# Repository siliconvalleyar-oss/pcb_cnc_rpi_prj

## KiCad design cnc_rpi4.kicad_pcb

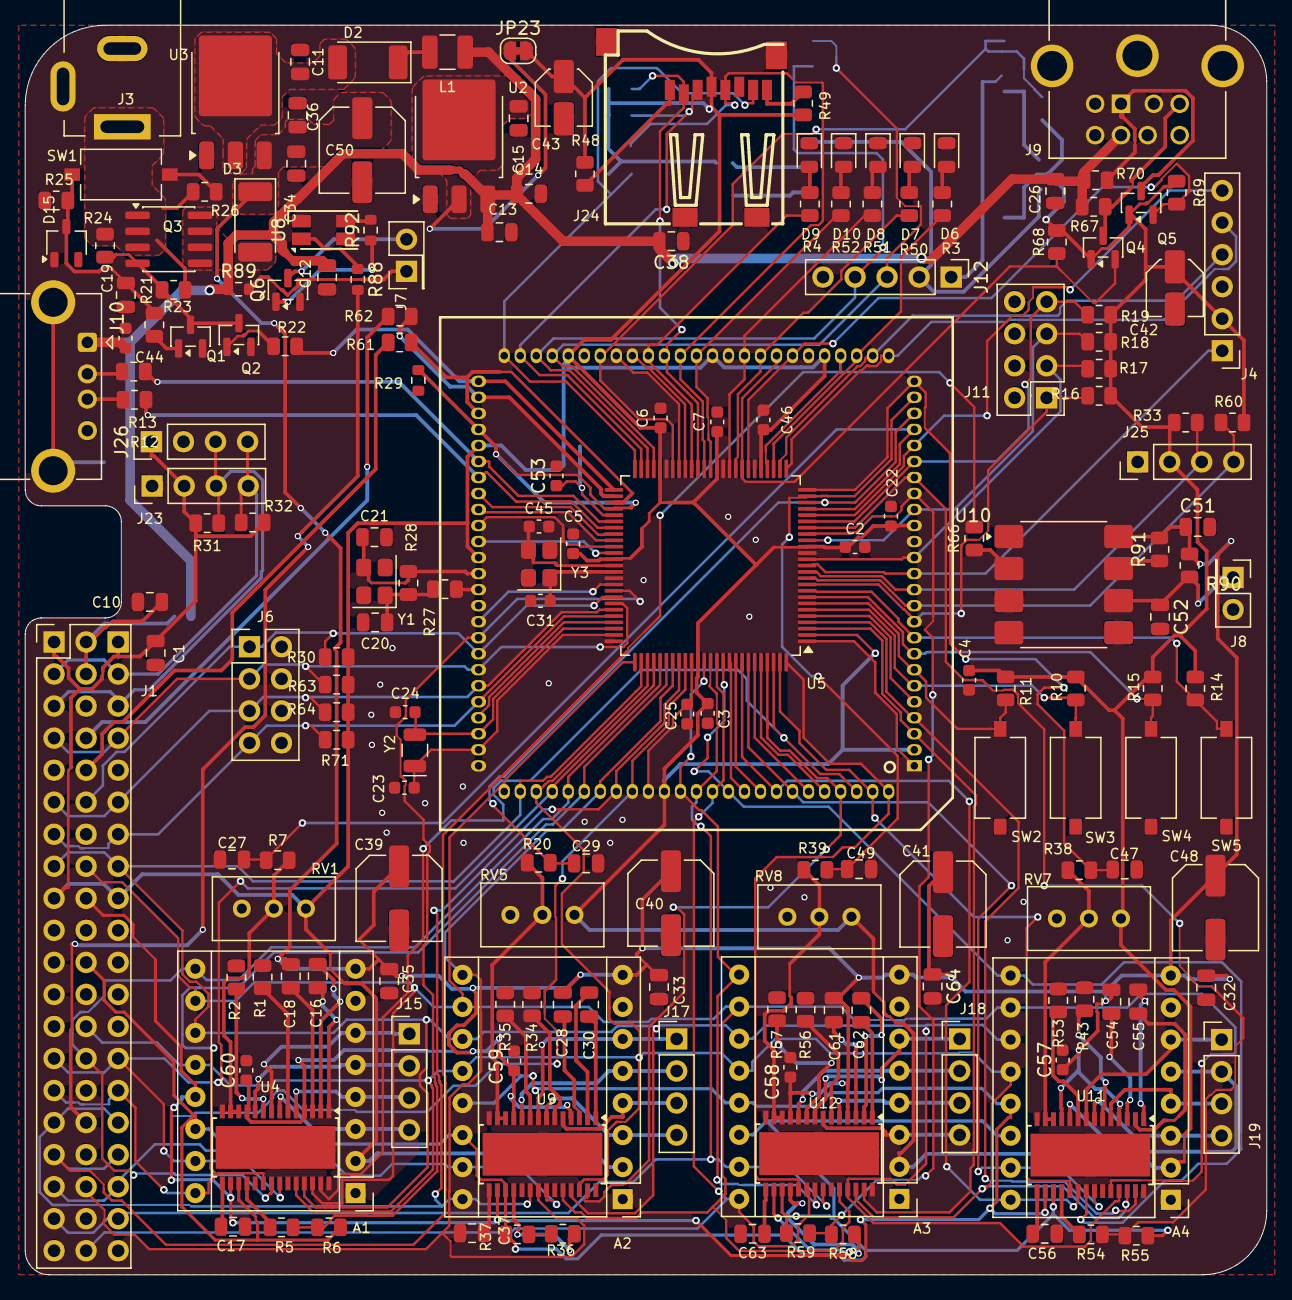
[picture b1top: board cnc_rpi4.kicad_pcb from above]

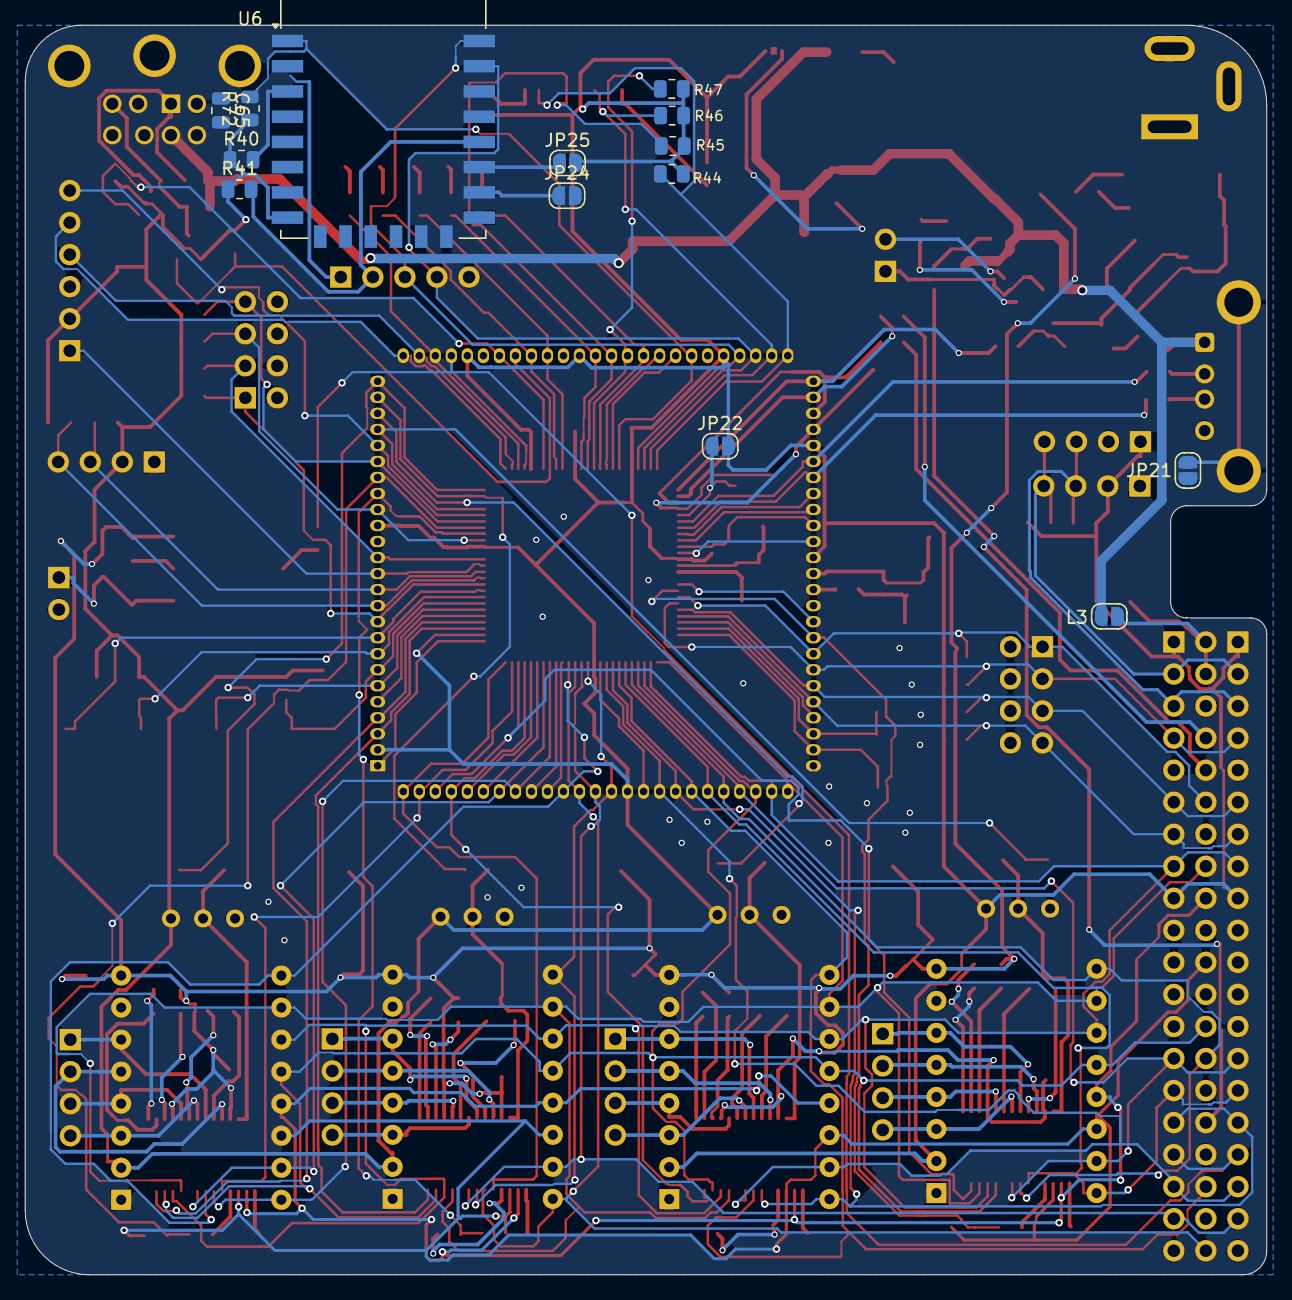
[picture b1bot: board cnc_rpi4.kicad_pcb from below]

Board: 2 copper layers, 98.4 x 99.1 mm, 202 parts (14 on the bottom side), 185 nets.

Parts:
A1, A2, A3, A4: Pololu_Breakout_A4988; Pololu_Breakout-16_15.2x20.3mm
C1, C10, C12, C13, C18, C19, C26, C27, C28, C29, C32, C33, C34, C35, C38, C47, C49, C51, C52, C54, C61, C64, C65: 100nf; C_0805_2012Metric
C2, C3, C4, C5, C6, C7, C22, C44, C57, C58, C59, C60: 100nf; C_0603_1608Metric
C11, C14, C15, C17, C36, C37, C56, C63: 4.7uf; C_0805_2012Metric
C16, C30, C55, C62: 10nf; C_0805_2012Metric
C20, C21: 15p; C_0805_2012Metric
C23, C24, C31, C45, C53: 15p; C_0603_1608Metric
C25, C46: 100; C_0603_1608Metric
C39, C40, C41, C48, C50: RVT100UF35V67RV0034; C_Elec_6.3x5.4
C42, C43: EFVH035ADA100M0454; C_Elec_4x5.4
D2, D3: 1N6858UR; D_MELF
D6, D7, D8, D9, D10: LED; D_0805_2012Metric
D15: D_Zener_Dual_CommonCathode_AAK_Split; TSOT-23
J1: Raspberry_Pi_4; Rpi_PinHeader_2x20_P2.54mm_Vertical
J3: PWR IN; BarrelJack_Kycon_KLDX-0202-xC_Horizontal
J4: icd; PinHeader_1x06_P2.54mm_Vertical
J6, J11: LIMITS; PinHeader_2x04_P2.54mm_Vertical
J7: Motor_1; PinHeader_2x01_P2.54mm_Vertical
J8: Motor_2; PinHeader_2x01_P2.54mm_Vertical
J9: Mini-DIN-6; MINIDIN6_TE_1658998-1
J10: USB_A; USB_A_Kycon_KUSBX-AS1N-B_Horizontal
J12: uart_programmer; PinHeader_1x05_P2.54mm_Vertical
J15, J17, J18, J19: pololu; PinHeader_1x04_P2.54mm_Vertical
J23, J25, J26: OLED SSD1306; PinHeader_1x04_P2.54mm_Vertical
J24: TF-001B
JP21, JP24, JP25: SolderJumper-2_P1.3mm_Open_RoundedPad1.0x1.5mm
JP22: usb_on; SolderJumper-2_P1.3mm_Open_RoundedPad1.0x1.5mm
JP23: 0; SolderJumper-2_P1.3mm_Bridged_RoundedPad1.0x1.5mm
L1: 100mh; L_1210_3225Metric
L3: 100mh; SolderJumper-2_P1.3mm_Open_RoundedPad1.0x1.5mm
Q1, Q2, Q6: BC847; SOT-23
Q3: IRF7404; SOIC-8_3.9x4.9mm_P1.27mm
Q4, Q5: 2N7002; SOT-23
R1, R2, R6, R34, R35, R37, R43, R53, R55, R56, R57, R59: 0.1r; R_0805_2012Metric
R3, R4, R31, R32, R50, R51, R52: 1k; R_0805_2012Metric
R5, R36, R54, R58: 1.5k; R_0805_2012Metric
R7, R20, R38, R39, R61, R62, R66, R67, R68, R69, R70, R90, R91: 100; R_0805_2012Metric
R10, R11, R14, R15, R33, R41, R44, R45, R46, R47, R48, R49, R60, R72: 2k2; R_0805_2012Metric
R12, R13, R40: 0; R_0805_2012Metric
R16, R17, R18, R19, R30, R63, R64, R71: 10k; R_0805_2012Metric
R21, R22: 10kr; R_0805_2012Metric
R23: 100K; R_0805_2012Metric
R24: 33K; R_0805_2012Metric
R25, R26: 100k; R_0805_2012Metric
R27: 1K; R_0805_2012Metric
R28: 1M; R_0805_2012Metric
R29: 0; R_0603_1608Metric
R88, R89, R92: 1k; R_0603_1608Metric
RV1, RV5, RV7, RV8: 10k Potentiometer_Trim_US; Potentiometer_Bourns_3296W_Vertical
SW1, SW2, SW3, SW4, SW5: K2-1107ST-A4SW-06; SW_Tactile_SPST_NO_Straight_CK_PTS636Sx25SMTRLFS
U1: PIC32MX795F512L-80x-PF; MA240011_Socket_TQFP100_100pin
U2: LM1117DT-3.3; TO-252-3_TabPin2
U3: LM1117DT-5.0; TO-252-3_TabPin2
U4, U9, U11, U12: DRV8825PWPR; HTSSOP-28-1EP_4.4x9.7mm_P0.65mm_EP3.4x9.5mm
U5: PIC32MX795F512L-80I_PF; TQFP-100_14x14mm_P0.5mm
U6: ESP-12E
U8: Optocoupler_DC_PhotoNPN_AKEC; Kingbright_KPS-3227
U10: 6N137S-TA1; SOP-8_6.605x9.655mm_P2.54mm
Y1, Y3: 8MHz SMD crystal oscillator ±10ppm ±30ppm SMD3225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; Crystal_SMD_3225-4Pin_3.2x2.5mm
Y2: Crystal_Small; Crystal_SMD_EuroQuartz_EQ161-2Pin_3.2x1.5mm

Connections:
+3V3: A1.2 (VDD), A2.2 (VDD), A3.2 (VDD), A4.2 (VDD), C1.1, C2.1, C3.1, C4.1, C5.1, C6.1, C7.1, C22.1, C42.1, C43.1, C46.1, J1.1 (3V3), J1.17 (3V3), J4.2, J23.2, J24.4 (VDD), J25.2, J26.1, JP22.2 (B), JP23.2 (B), JP25.2 (B), Q4.1 (G), Q5.1 (G), R10.1, R11.1, R14.1, R15.1, R16.1, R17.1, R18.1, R19.1, R30.1, R31.1, R32.1, R33.1, R40.1, R41.1, R44.2, R45.2, R46.2, R47.2, R48.2, R49.1, R60.1, R63.1, R64.1, R68.2, R69.2, R71.1, R72.1, RV1.1, RV5.1, RV7.1, RV8.1, U1.2 (VDD), U1.16 (VDD), U1.30 (AVDD), U1.37 (VDD), U1.46 (VDD), U1.55 (VUSB3V3), U1.62 (VDD), U1.86 (VDD), U5.2 (VDD), U5.16 (VDD), U5.30 (AVDD), U5.37 (VDD), U5.46 (VDD), U5.62 (VDD), U5.86 (VDD), U6.8 (VCC)
+5V: C12.1, C13.1, C14.2, C26.1, C38.2, C44.2, J9.4, J10.1 (VBUS), L1.2, L3.2, R67.2, R70.2, R89.1, U2.3 (VI)
/ANALOG_1: C27.1, R7.1, U1.22 (RB3), U5.22 (AN3/C2IN+/CN5/RB3)
/ANALOG_2: C29.1, R20.1, U1.23 (RB2), U5.23 (AN2/C2IN-/CN4/RB2)
/ANALOG_3: C49.1, R39.1, U1.24 (PGEC1/RB1), U5.24 (PGEC1/AN1/CN3/RB1)
/ANALOG_4: C47.1, R38.1, U1.25 (PGED1/RB0), U5.25 (PGED1/AN0/CN2/RB0)
/GPIO2_SDA: J1.3 (SDA_I2C1/GPIO02), J23.4, J26.4, R32.2
/GPIO3_SCL: J1.5 (SCL_I2C1/GPIO03), J23.3, J26.3, R31.2
/LED_a: R3.1, U1.28 (RA9), U5.28 (VREF-/CVREF-/AERXD2/PMA7/RA9)
/LED_b: R50.1, U1.34 (RB10), U5.34 (AN10/CVREFOUT/PMA13/RB10)
/LED_c: R51.1, U1.35 (RB11), U5.35 (AN11/ERXERR/AETXERR/PMA12/RB11)
/LED_d: R4.1, U1.41 (RB12), U5.41 (AN12/ERXD0/AECRS/PMA11/RB12)
/LED_e: R52.1, U1.38 (RA1/TCK), U5.38 (TCK/RA1)
/MCU/5VCC: C10.1, J1.2 (5V), J1.4 (5V), L3.1
/MS1: A1.10 (MS1), A2.10 (MS1), A3.10 (MS1), A4.10 (MS1), J1.16 (GPIO23/SDIO_CMD), U1.76 (RD1), U4.26 (MODE2), U5.76 (OC2/RD1), U9.24 (MODE0), U11.24 (MODE0), U12.24 (MODE0)
/MS2: A1.11 (MS2), A2.11 (MS2), A3.11 (MS2), A4.11 (MS2), J1.15 (GPIO22/SDIO_CLK), U1.77 (RD2), U4.25 (MODE1), U5.77 (OC3/RD2), U9.25 (MODE1), U11.25 (MODE1), U12.25 (MODE1)
/MS3: A1.12 (MS3), A2.12 (MS3), A3.12 (MS3), A4.12 (MS3), J1.26 (~CE1_SPI0/GPIO07), U1.78 (RD3), U4.24 (MODE0), U5.78 (OC4/RD3), U9.26 (MODE2), U11.26 (MODE2), U12.26 (MODE2)
/M_Rx: J1.10 (GPIO15/UART_RXD), R61.1
/M_Tx: J1.8 (GPIO14/UART_TXD), R62.1
/PIC32_SCL: J25.3, R33.2, U1.12 (RG8), U5.12 (ERXDV/AERXDV/ECRSDV/AECRSDV/SCL4/SDO2/U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)
/PIC32_SDA: J25.4, R60.2, U1.11 (RG7), U5.11 (ECRS/SDA4/SDI2/U3RX/PMA4/CN9/RG7)
/PS2_CLK: Q4.2 (S), R68.1, U1.33 (RB9), U5.33 (AN9/C2OUT/RB9)
/PS2_DATA: Q5.2 (S), R69.1, U1.32 (RB8), U5.32 (AN8/C1OUT/RB8)
/PWR_SIGNAL: R22.1, U1.51 (RF3), U5.51 (USBID/RF3)
/Pololu/IC4_dir: A4.16 (DIR), U1.93 (RE0), U5.93 (PMD0/RE0), U11.20 (DIR)
/Pololu/IC4_enable: A4.9 (~ENABLE), U1.90 (RG0), U5.90 (C2RX/PMD8/RG0), U11.21 (NENBL)
/Pololu/IC4_step: A4.15 (STEP), U1.94 (RE1), U5.94 (PMD1/RE1), U11.22 (STEP)
/RA6: U1.91 (RA6/TRCLK), U5.91 (TRCLK/RA6), U9.19 (DECAY)
/RA7: U1.92 (RA7/TRD3), U4.19 (DECAY), U5.92 (TRD3/RA7)
/RE2: U1.98 (RE2), U4.27 (nHOME), U5.98 (PMD2/RE2)
/RE3: U1.99 (RE3), U5.99 (PMD3/RE3), U11.19 (DECAY)
/RE4: U1.100 (RE4), U5.100 (PMD4/RE4), U12.19 (DECAY)
/RE5: U1.3 (RE5), U5.3 (PMD5/RE5), U12.27 (nHOME)
/RE6: U1.4 (RE6), U5.4 (PMD6/RE6), U11.27 (nHOME)
/RG13: U1.97 (RG13/TRD0), U5.97 (TRD0/RG13), U9.27 (nHOME)
/dir_1: A1.16 (DIR), J1.29 (GPCLK1/GPIO05), U1.81 (RD4), U4.20 (DIR), U5.81 (OC5/PMWR/CN13/RD4)
/dir_2: A2.16 (DIR), J1.31 (GPCLK2/GPIO06), U1.83 (RD6), U5.83 (ETXEN/PMD14/CN15/RD6), U9.20 (DIR)
/dir_3: A3.16 (DIR), J1.40 (GPIO21/SPI1_SCLK/PCM_DOUT), U1.89 (RG1), U5.89 (C2TX/ETXERR/PMD9/RG1), U12.20 (DIR)
/en_1: A1.9 (~ENABLE), J1.28 (ID_SC_I2C0/GPIO01), U1.80 (RD13), U4.21 (NENBL), U5.80 (ETXD3/PMD13/CN19/RD13)
/en_2: A2.9 (~ENABLE), J1.36 (GPIO16/SPI1_~CE2), U1.82 (RD5), U5.82 (PMRD/CN14/RD5), U9.21 (NENBL)
/en_3: A3.9 (~ENABLE), J1.38 (GPIO20/SPI1_MOSI/PCM_DIN/PWM1), U1.87 (RF0), U5.87 (C1RX/ETXD1/PMD11/RF0), U12.21 (NENBL)
/esp8266mod/FLASH_esp: J12.2, R41.2, U6.18 (GPIO0)
/esp8266mod/RST_esp: C65.1, R72.2, U1.44 (RB15), U5.44 (AN15/ERXD3/AETXD2/OCFB/PMALL/PMA0/CN12/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), U6.1 (~RST)
/esp8266mod/RXD_esp: J12.4, U1.48 (RD15), U5.48 (AETXD1/SCK3/U4TX/~U1RTS/CN21/RD15), U6.21 (GPIO3/RXD)
/esp8266mod/TDX_esp: J12.3, U1.47 (RD14), U5.47 (AETXD0/~SS3/U4RX/~U1CTS/CN20/RD14), U6.22 (GPIO1/TXD)
/flt_1: R5.2, R6.2, U1.67 (RA15), U5.67 (AETXEN/SDA1/INT4/RA15)
/flt_2: R36.2, R37.2, U1.66 (RA14), U5.66 (AETXCLK/SCL1/INT3/RA14)
/flt_3: R58.2, R59.2, U1.18 (RE8), U5.18 (AERXD0/INT1/RE8)
/flt_4: R54.2, R55.1, U1.19 (RE9), U5.19 (AERXD1/INT2/RE9)
/limit_1: J11.1, R16.2, U1.10 (RG6), U5.10 (ECOL/SCK2/U6TX/~U3RTS/PMA5/CN8/RG6)
/limit_2: J11.3, R17.2, U1.14 (RG9), U5.14 (ERXCLK/AERXCLK/EREFCLK/AEREFCLK/~SS2/U6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)
/limit_3: J11.5, R18.2, U1.17 (RA0/TMS), U5.17 (TMS/RA0)
/limit_4: J11.7, R19.2, U1.20 (RB5), U5.20 (AN5/C1IN+/VBUSON/CN7/RB5)
/limit_pi1: J1.12 (GPIO18/SPI1_~CE0/PCM_CLK/PWM0), J6.1, R30.2, U1.68 (RD8), U5.68 (RTCC/EMDIO/AEMDIO/IC1/RD8)
/limit_pi2: J1.7 (GPCLK0/GPIO04), J6.3, R63.2, U1.69 (RD9), U5.69 (~SS1/IC2/RD9)
/limit_pi3: J1.11 (GPIO17/SPI1_~CE1), J6.5, R64.2, U1.70 (RD10), U5.70 (SCK1/IC3/PMCS2/PMA15/RD10)
/limit_pi4: J1.13 (GPIO27/SDIO_DAT3), J6.7, R71.2, U1.71 (RD11), U5.71 (EMDC/AEMDC/IC4/PMCS1/PMA14/RD11)
/motor_control_1: J1.32 (GPIO12/PWM0), R88.2
/motor_control_2: J1.33 (GPIO13/PWM1), R66.2, U1.29 (RA10), U5.29 (VREF+/CVREF+/AERXD3/PMA6/RA10)
/pic32/D+: R12.1, U1.57 (RG2/D+), U5.57 (D+/RG2)
/pic32/D-: R13.1, U1.56 (RG3/D-), U5.56 (D-/RG3)
/pic32/MCLR: J4.1, U1.13 (~MCLR), U5.13 (~MCLR)
/pic32/OSC1: C21.1, R28.2, U1.63 (RC12/OSC1/CLK), Y1.3
/pic32/OSC1_B: C45.1, U5.63 (OSC1/CLKI/RC12), Y3.3
/pic32/OSC2: R27.1, U1.64 (RC15/OSC2/CLKO)
/pic32/OSC2_B: C31.1, U5.64 (OSC2/CLKO/RC15), Y3.1
/pic32/PGC: J4.5, U1.26 (PGEC2/RB6), U5.26 (PGEC2/AN6/OCFA/RB6)
/pic32/PGD: J4.4, U1.27 (PGED2/RB7), U5.27 (PGED2/AN7/RB7)
/pic32/PGM: J4.6, U1.21 (RB4), U5.21 (AN4/C1IN-/CN6/RB4)
/pic32/RA2: U1.58 (RA2), U5.58 (SCL2/RA2)
/pic32/RA3: U1.59 (RA3), U5.59 (SDA2/RA3)
/pic32/RA4: U1.60 (RA4/TDI), U5.60 (TDI/RA4)
/pic32/RA5: U1.61 (RA5/TDO), U5.61 (TDO/RA5)
/pic32/RB13: U1.42 (RB13), U5.42 (AN13/ERXD1/AECOL/PMA10/RB13)
/pic32/RB14: U1.43 (RB14), U5.43 (AN14/ERXD2/AETXD3/PMALH/PMA1/RB14)
/pic32/RD0: U1.72 (RD0), U5.72 (SDO1/OC1/INT0/RD0)
/pic32/RE7: U1.5 (RE7), U5.5 (PMD7/RE7)
/pic32/RF2: R62.2, U1.52 (RF2), U5.52 (SDA3/SDI3/U1RX/RF2)
/pic32/RF4: J24.3 (CMD), R46.1, U1.49 (RF4), U5.49 (SDA5/SDI4/U2RX/PMA9/CN17/RF4)
/pic32/RF5: J24.7 (DAT0), R44.1, U1.50 (RF5), U5.50 (SCL5/SDO4/U2TX/PMA8/CN18/RF5)
/pic32/RF8: R61.2, U1.53 (RF8), U5.53 (SCL3/SDO3/U1TX/RF8)
/pic32/RF12: J24.2 (DAT3/CD), R47.1, U1.40 (RF12), U5.40 (AC1RX/~SS4/U5RX/~U2CTS/RF12)
/pic32/RF13: J24.5 (CLK), R45.1, U1.39 (RF13), U5.39 (AC1TX/SCK4/U5TX/~U2RTS/RF13)
/pic32/RG12: U1.96 (RG12/TRD1), U5.96 (TRD1/RG12)
/pic32/RG14: U1.95 (RG14/TRD2), U5.95 (TRD2/RG14)
/pic32/RG15: U1.1 (RG15), U5.1 (AERXERR/RG15)
/pic32/USB_D+: J10.3 (D+), R12.2
/pic32/USB_D-: J10.2 (D-), R13.2
/pic32/VBUS_: R29.1, U1.54 (VBUS), U5.54 (VBUS)
/pic32/VDD_CORE: C25.1, U1.85 (VCAP/VDDCORE), U5.85 (VCAP/VDDCORE)
/pic32/VUSB3V3: C53.1, JP22.1 (A), U5.55 (VUSB3V3)
/pic32/osc_1: C24.1, U1.73 (RC13/SOSCI), U5.73 (SOSCI/CN1/RC13), Y2.2
/pic32/osc_2: C23.1, U1.74 (RC14/SOSCO), U5.74 (SOSCO/T1CK/CN0/RC14), Y2.1
/power/V_IN1: D3.2 (A), Q3.5 (D), Q3.6 (D), Q3.7 (D), Q3.8 (D)
/power/V_INUPT: J3.1 (In), Q3.1 (S), Q3.2 (S), Q3.3 (S), R23.1, R24.2, R26.2
/power/vout_lm1117_3v3: C15.2, JP23.1 (A), U2.2 (VO)
/power/vout_lm1117_5v: C11.1, D2.2 (A), U3.2 (VO)
/reset: A1.13 (~RESET), A2.13 (~RESET), A3.13 (~RESET), A4.13 (~RESET), J1.18 (GPIO24/SDIO_DAT0), U4.16 (nRESET), U9.16 (nRESET), U11.16 (nRESET), U12.16 (nRESET)
/sleep: A1.14 (~SLEEP), A2.14 (~SLEEP), A3.14 (~SLEEP), A4.14 (~SLEEP), J1.22 (GPIO25/SDIO_DAT1), R6.1, R37.1, R55.2, R59.1, U4.17 (nSLEEP), U9.17 (nSLEEP), U11.17 (nSLEEP), U12.17 (nSLEEP)
/step_1: A1.15 (STEP), J1.27 (ID_SD_I2C0/GPIO00), U1.79 (RD12), U4.22 (STEP), U5.79 (ETXD2/IC5/PMD12/RD12)
/step_2: A2.15 (STEP), J1.35 (GPIO19/SPI1_MISO/PCM_FS), U1.84 (RD7), U5.84 (ETXCLK/PMD15/CN16/RD7), U9.22 (STEP)
/step_3: A3.15 (STEP), J1.37 (GPIO26/SDIO_DAT2), U1.88 (RF1), U5.88 (C1TX/ETXD0/PMD10/RF1), U12.22 (STEP)
/switch_a: R11.2, SW2.1, U1.7 (RC2), U5.7 (T3CK/AC2TX/RC2)
/switch_b: R10.2, SW3.1, U1.6 (RC1), U5.6 (T2CK/RC1)
/switch_c: R15.2, SW4.1, U1.8 (RC3), U5.8 (T4CK/AC2RX/RC3)
/switch_d: R14.2, SW5.1, U1.9 (RC4), U5.9 (T5CK/SDI1/RC4)
GND: A1.1 (GND), A1.7 (GND), A2.1 (GND), A2.7 (GND), A3.1 (GND), A3.7 (GND), A4.1 (GND), A4.7 (GND), C1.2, C2.2, C3.2, C4.2, C5.2, C6.2, C7.2, C10.2, C11.2, C12.2, C13.2, C14.1, C15.1, C17.2, C19.2, C20.2, C21.2, C22.2, C23.2, C24.2, C25.2, C26.2, C27.2, C29.2, C31.2, C32.2, C33.2, C34.2, C35.2, C36.2, C37.2, C38.1, C39.2, C40.2, C41.2, C42.2, C43.2, C44.1, C45.2, C46.2, C47.2, C48.2, C49.2, C50.2, C51.2, C52.2, C53.2, C56.2, C57.2, C58.2, C59.2, C60.2, C63.2, C64.2, D6.1 (K), D7.1 (K), D8.1 (K), D9.1 (K), D10.1 (K), D15.1 (A), J1.6 (GND), J1.9 (GND), J1.14 (GND), J1.20 (GND), J1.25 (GND), J1.30 (GND), J1.34 (GND), J1.39 (GND), J3.2 (Ext), J4.3, J6.2, J6.4, J6.6, J6.8, J8.2, J9.3, J10.4 (GND), J11.2, J11.4, J11.6, J11.8, J12.5, J23.1, J24.6 (VSS), J24.SH (SHIELD), J25.1, J26.2, JP21.2 (B), JP24.2 (B), Q1.2 (E), Q2.2 (E), Q6.2 (E), R1.2, R2.1, R25.1, R34.2, R35.1, R43.2, R53.1, R56.2, R57.1, RV1.3, RV5.3, RV7.3, RV8.3, SW2.2, SW3.2, SW4.2, SW5.2, U1.15 (VSS), U1.31 (AVSS), U1.36 (VSS), U1.45 (VSS), U1.65 (VSS), U1.75 (VSS), U2.1 (GND), U3.1 (GND), U4.14 (GND), U4.28 (GND), U4.29 (EP), U5.15 (VSS), U5.31 (AVSS), U5.36 (VSS), U5.45 (VSS), U5.65 (VSS), U5.75 (VSS), U6.15 (GND), U8.2, U8.3, U9.14 (GND), U9.28 (GND), U9.29 (EP), U10.3, U10.5, U11.14 (GND), U11.28 (GND), U11.29 (EP), U12.14 (GND), U12.28 (GND), U12.29 (EP), Y1.2, Y1.4, Y3.2, Y3.4
IC1_1A: A1.4 (1A), J15.3, U4.5 (AOUT1)
IC1_1B: A1.3 (1B), J15.4, U4.7 (AOUT2)
IC1_2A: A1.5 (2A), J15.2, U4.10 (BOUT1)
IC1_2B: A1.6 (2B), J15.1, U4.8 (BOUT2)
IC2_1A: A2.4 (1A), J17.3, U9.5 (AOUT1)
IC2_1B: A2.3 (1B), J17.4, U9.7 (AOUT2)
IC2_2A: A2.5 (2A), J17.2, U9.10 (BOUT1)
IC2_2B: A2.6 (2B), J17.1, U9.8 (BOUT2)
IC3_1A: A3.4 (1A), J18.3, U12.5 (AOUT1)
IC3_1B: A3.3 (1B), J18.4, U12.7 (AOUT2)
IC3_2A: A3.5 (2A), J18.2, U12.10 (BOUT1)
IC3_2B: A3.6 (2B), J18.1, U12.8 (BOUT2)
IC4_1A: A4.4 (1A), J19.3, U11.5 (AOUT1)
IC4_1B: A4.3 (1B), J19.4, U11.7 (AOUT2)
IC4_2A: A4.5 (2A), J19.2, U11.10 (BOUT1)
IC4_2B: A4.6 (2B), J19.1, U11.8 (BOUT2)
unnamed: C20.1, R27.2, R28.1, Y1.1
unnamed: D2.1 (K), L1.1
unnamed: D6.2 (A), R3.2
unnamed: D7.2 (A), R50.2
unnamed: D8.2 (A), R51.2
unnamed: D9.2 (A), R4.2
unnamed: D10.2 (A), R52.2
unnamed: C19.1, D15.3 (K), R21.1, R25.2, SW1.2
unnamed: J7.1, R89.2
unnamed: J7.2, Q6.3 (C)
unnamed: C52.1, J8.1, R90.1, U10.6
unnamed: J10.SH (Shield), JP21.1 (A)
unnamed: C65.2, J12.1
unnamed: J24.8 (DAT1), R49.2
unnamed: J24.1 (DAT2), R48.1
unnamed: JP24.1 (A), U6.16 (GPIO15)
unnamed: JP25.1 (A), U6.17 (GPIO2)
unnamed: Q1.1 (B), R21.2
unnamed: Q1.3 (C), Q2.3 (C), Q3.4 (G), R23.2, R24.1
unnamed: Q2.1 (B), R22.2
unnamed: J9.5, Q4.3 (D), R67.1
unnamed: J9.1, Q5.3 (D), R70.1
unnamed: Q6.1 (B), R92.1
unnamed: R26.1, SW1.1
unnamed: R66.1, U10.2
unnamed: R88.1, U8.1
unnamed: R91.1, U10.7
unnamed: R92.2, U8.4
unnamed: R7.2, RV1.2, U4.12 (AVREF), U4.13 (BVREF)
unnamed: C16.1, U4.1 (CP1)
unnamed: C16.2, U4.2 (CP2)
unnamed: R1.1, U4.6 (ISENA)
unnamed: R2.2, U4.9 (ISENB)
unnamed: C17.1, U4.15 (V3P3OUT)
unnamed: C18.2, U4.3 (VCP)
unnamed: R5.1, U4.18 (nFAULT)
unnamed: R40.2, U6.3 (EN)
unnamed: R20.2, RV5.2, U9.12 (AVREF), U9.13 (BVREF)
unnamed: C30.1, U9.1 (CP1)
unnamed: C30.2, U9.2 (CP2)
unnamed: R34.1, U9.6 (ISENA)
unnamed: R35.2, U9.9 (ISENB)
unnamed: C37.1, U9.15 (V3P3OUT)
unnamed: C28.2, U9.3 (VCP)
unnamed: R36.1, U9.18 (nFAULT)
unnamed: R38.2, RV7.2, U11.12 (AVREF), U11.13 (BVREF)
unnamed: C55.1, U11.1 (CP1)
unnamed: C55.2, U11.2 (CP2)
unnamed: R43.1, U11.6 (ISENA)
unnamed: R53.2, U11.9 (ISENB)
unnamed: C56.1, U11.15 (V3P3OUT)
unnamed: C54.2, U11.3 (VCP)
unnamed: R54.1, U11.18 (nFAULT)
unnamed: R39.2, RV8.2, U12.12 (AVREF), U12.13 (BVREF)
unnamed: C62.1, U12.1 (CP1)
unnamed: C62.2, U12.2 (CP2)
unnamed: R56.1, U12.6 (ISENA)
unnamed: R57.2, U12.9 (ISENB)
unnamed: C63.1, U12.15 (V3P3OUT)
unnamed: C61.2, U12.3 (VCP)
unnamed: R58.1, U12.18 (nFAULT)
VCC: A1.8 (VMOT), A2.8 (VMOT), A3.8 (VMOT), A4.8 (VMOT), C18.1, C28.1, C32.1, C33.1, C34.1, C35.1, C36.1, C39.1, C40.1, C41.1, C48.1, C50.1, C51.1, C54.1, C57.1, C58.1, C59.1, C60.1, C61.1, C64.1, D3.1 (K), R90.2, R91.2, U3.3 (VI), U4.4 (VMA), U4.11 (VMB), U9.4 (VMA), U9.11 (VMB), U10.8, U11.4 (VMA), U11.11 (VMB), U12.4 (VMA), U12.11 (VMB)

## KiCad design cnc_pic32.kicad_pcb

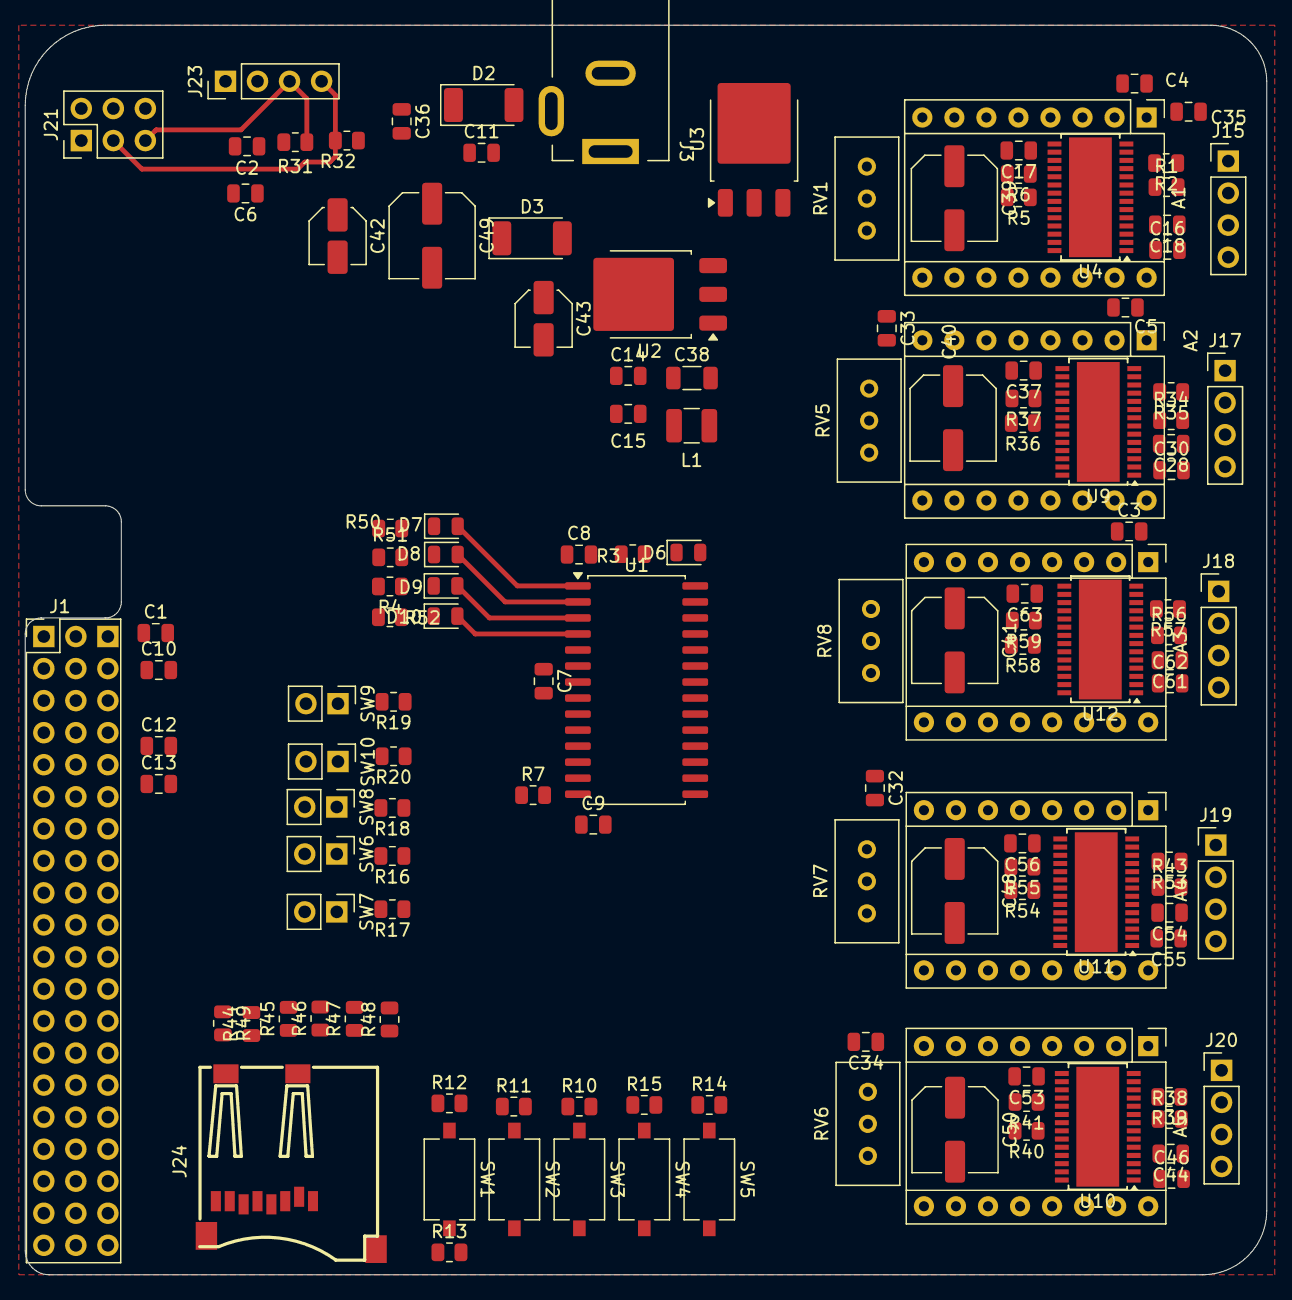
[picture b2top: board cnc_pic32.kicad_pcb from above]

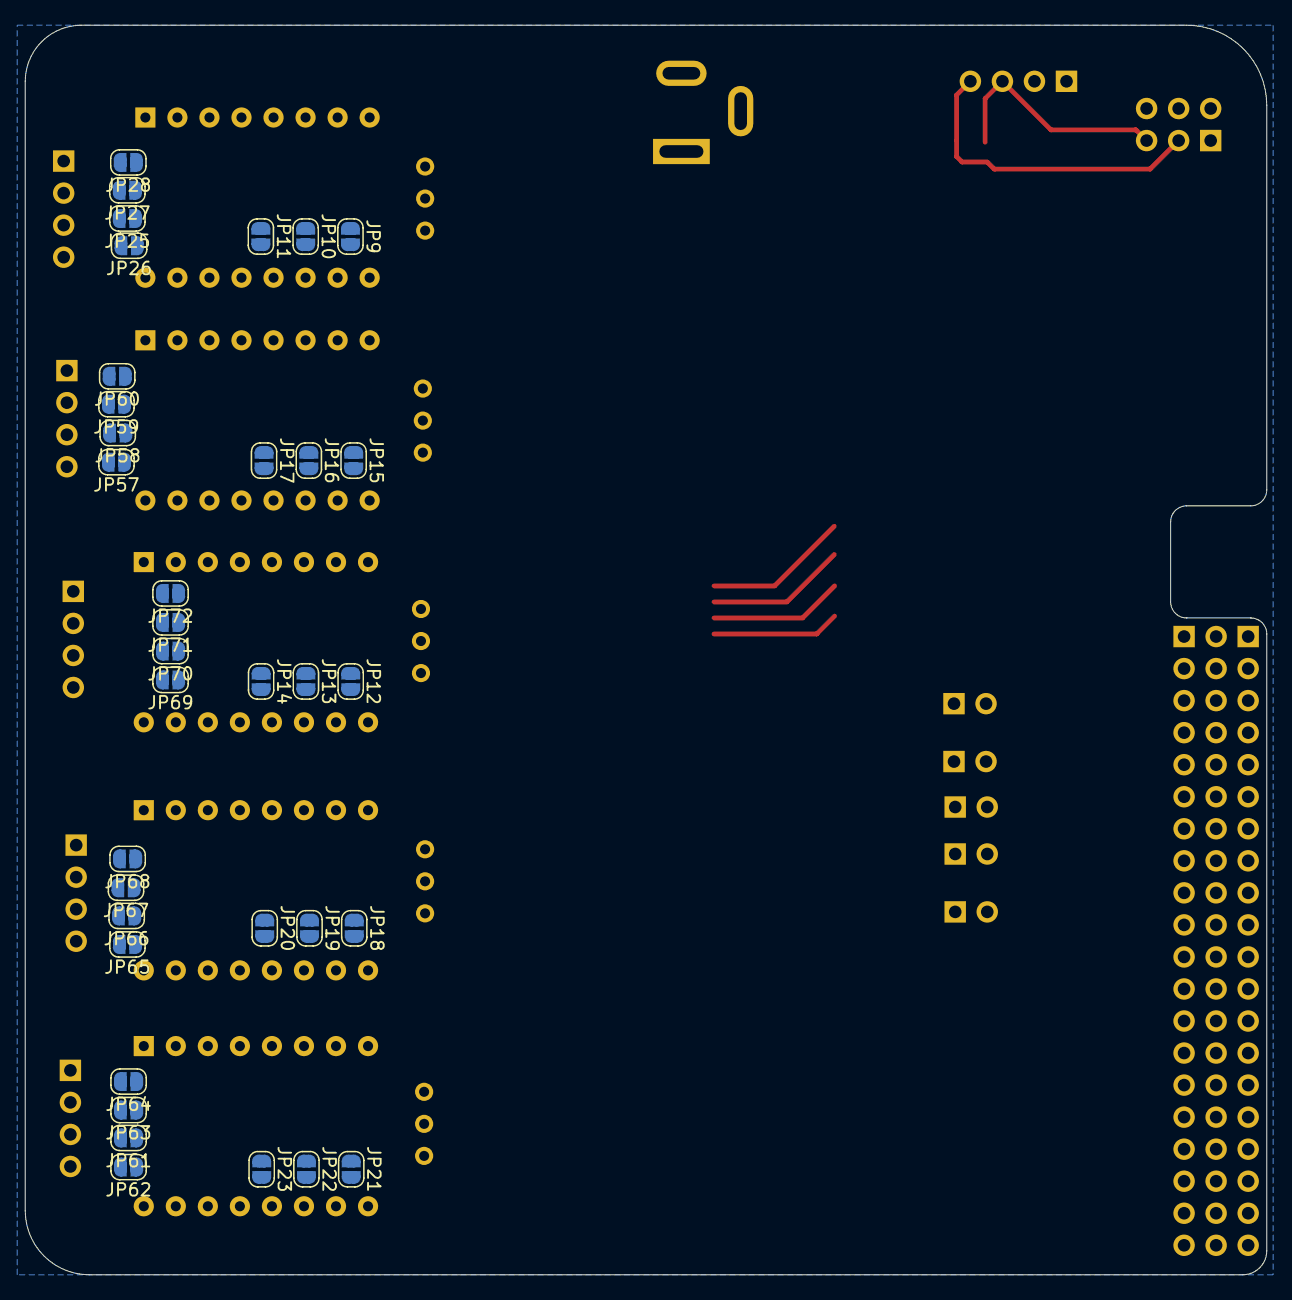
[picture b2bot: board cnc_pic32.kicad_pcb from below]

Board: 2 copper layers, 98.4 x 99.1 mm, 170 parts (35 on the bottom side), 158 nets.

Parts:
A1, A2, A3, A4, A5: Pololu_Breakout_A4988; Pololu_Breakout-16_15.2x20.3mm
C1, C2, C3, C4, C5, C6, C7, C8, C9, C10, C11, C12, C13, C18, C28, C32, C33, C34, C35, C44, C54, C61: 100nf; C_0805_2012Metric
C14, C15, C17, C36, C37, C53, C56, C63: 4.7uf; C_0805_2012Metric
C16, C30, C46, C55, C62: 10nf; C_0805_2012Metric
C38: 100nf; C_1206_3216Metric
C39, C40, C41, C48, C49, C50: RVT100UF35V67RV0034; C_Elec_6.3x5.4
C42, C43: EFVH035ADA100M0454; C_Elec_4x5.4
D2, D3: 1N6858UR; D_MELF
D6, D7, D8, D9, D10: LED; D_0805_2012Metric
J1: Raspberry_Pi_4; Rpi_PinHeader_2x20_P2.54mm_Vertical
J3: Connector Power; BarrelJack_Kycon_KLDX-0202-xC_Horizontal
J15, J17, J18, J19, J20: pololu; PinHeader_1x04_P2.54mm_Vertical
J21: conector oled ST1306 128x32; PinHeader_2x03_P2.54mm_Vertical
J23: OLED SSD1306; PinHeader_1x04_P2.54mm_Vertical
J24: TF-001B
JP9, JP12, JP15, JP18, JP21: MS1; SolderJumper-2_P1.3mm_Open_RoundedPad1.0x1.5mm
JP10, JP13, JP16, JP19, JP22: MS2; SolderJumper-2_P1.3mm_Open_RoundedPad1.0x1.5mm
JP11, JP14, JP17, JP20, JP23, JP25, JP26, JP27, JP28, JP57, JP58, JP59, JP60, JP61, JP62, JP63, JP64, JP65, JP66, JP67, JP68, JP69, JP70, JP71, JP72: MS3; SolderJumper-2_P1.3mm_Open_RoundedPad1.0x1.5mm
L1: 100mh; L_1210_3225Metric
R1, R2, R6, R7, R34, R35, R37, R38, R39, R41, R43, R53, R55, R56, R57, R59: 0.1r; R_0805_2012Metric
R3, R4, R31, R32, R50, R51, R52: 1k; R_0805_2012Metric
R5, R36, R40, R54, R58: 1.5k; R_0805_2012Metric
R10, R11, R12, R13, R14, R15, R44, R45, R46, R47, R48, R49: 2k2; R_0805_2012Metric
R16, R17, R18, R19, R20: 10k; R_0805_2012Metric
RV1, RV5, RV6, RV7, RV8: 10k Potentiometer_Trim_US; Potentiometer_Bourns_3296W_Vertical
SW1, SW2, SW3, SW4, SW5: K2-1107ST-A4SW-06; SW_Tactile_SPST_NO_Straight_CK_PTS636Sx25SMTRLFS
SW6, SW7, SW8, SW9, SW10: sw_limit; PinHeader_1x02_P2.54mm_Vertical
U1: MCP23017x-x-ML; SOIC-28W_7.5x17.9mm_P1.27mm
U2: LM1117DT-3.3; TO-252-3_TabPin2
U3: LM1117DT-5.0; TO-252-3_TabPin2
U4, U9, U10, U11, U12: DRV8825PWPR; HTSSOP-28-1EP_4.4x9.7mm_P0.65mm_EP3.4x9.5mm

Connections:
+3.3V: A1.2 (VDD), A2.2 (VDD), A3.2 (VDD), A4.2 (VDD), A5.2 (VDD), C1.1, C2.1, C3.1, C4.1, C5.1, C6.1, C7.1, C8.1, C9.1, C42.1, C43.1, J1.1 (3V3), J1.17 (3V3), J21.1, J23.2, R7.1, R10.1, R11.1, R14.1, R15.1, R16.1, R17.1, R18.1, R19.1, R20.1, R31.1, R32.1, RV1.1, RV5.1, RV6.1, RV7.1, RV8.1, U1.5 (V_{DD})
+3V3: C15.2, J24.4 (VDD), R44.2, R45.2, R46.2, R47.2, R48.2, R49.1, U2.2 (VO)
+5V: C10.1, C12.1, C13.1, D2.1 (K), J1.2 (5V), J1.4 (5V), L1.1
/LED_a: D6.2 (A), U1.28 (GPB3)
/LED_b: D7.2 (A), U1.1 (GPB4)
/LED_c: D8.2 (A), U1.2 (GPB5)
/LED_d: D9.2 (A), U1.3 (GPB6)
/LED_e: D10.2 (A), U1.4 (GPB7)
/M1: J1.10 (GPIO15/UART_RXD), JP9.1 (A), JP12.1 (A), JP15.1 (A), JP18.1 (A), JP21.1 (A)
/M2: J1.33 (GPIO13/PWM1), JP10.1 (A), JP13.1 (A), JP16.1 (A), JP19.1 (A), JP22.1 (A)
/M3: J1.8 (GPIO14/UART_TXD), JP11.1 (A), JP14.1 (A), JP17.1 (A), JP20.1 (A), JP23.1 (A)
/MCU/CE0: J1.24 (~CE0_SPI0/GPIO08), J24.2 (DAT3/CD), R47.1
/MCU/MISO: J1.21 (MISO_SPI0/GPIO09), J24.7 (DAT0), R44.1
/MCU/MOSI: J1.19 (MOSI_SPI0/GPIO10), J24.3 (CMD), R46.1
/MCU/SCLK: J1.23 (SCLK_SPI0/GPIO11), J24.5 (CLK), R45.1
/Oled/SCL: J1.5 (SCL_I2C1/GPIO03), J21.5, J23.3, R31.2, U1.8 (SCK)
/Oled/SDA: J1.3 (SDA_I2C1/GPIO02), J21.3, J23.4, R32.2, U1.9 (SDA)
/Pololu/FLT_4: R54.2, R55.2, U1.26 (GPB1)
/Pololu/FLT_5: R40.2, R41.2, U1.27 (GPB2)
/Pololu/IC1_1A: A1.4 (1A), J15.3, JP26.2 (B)
/Pololu/IC1_1B: A1.3 (1B), J15.4, JP25.2 (B)
/Pololu/IC1_2A: A1.5 (2A), J15.2, JP28.2 (B)
/Pololu/IC1_2B: A1.6 (2B), J15.1, JP27.2 (B)
/Pololu/IC1_MS1_DRV8825: A1.12 (MS3), JP11.2 (B), U4.24 (MODE0)
/Pololu/IC1_MS2_DRV8825: A1.11 (MS2), JP10.2 (B), U4.25 (MODE1)
/Pololu/IC1_MS3_DRV8825: A1.10 (MS1), JP9.2 (B), U4.26 (MODE2)
/Pololu/IC1_dir: A1.16 (DIR), J1.13 (GPIO27/SDIO_DAT3), U4.20 (DIR)
/Pololu/IC1_enable: A1.9 (~ENABLE), J1.27 (ID_SD_I2C0/GPIO00), U4.21 (NENBL)
/Pololu/IC1_step: A1.15 (STEP), J1.12 (GPIO18/SPI1_~CE0/PCM_CLK/PWM0), U4.22 (STEP)
/Pololu/IC2_1A: A2.4 (1A), J17.3, JP57.2 (B)
/Pololu/IC2_1B: A2.3 (1B), J17.4, JP58.2 (B)
/Pololu/IC2_2A: A2.5 (2A), J17.2, JP60.2 (B)
/Pololu/IC2_2B: A2.6 (2B), J17.1, JP59.2 (B)
/Pololu/IC2_dir: A2.16 (DIR), J1.18 (GPIO24/SDIO_DAT0), U9.20 (DIR)
/Pololu/IC2_enable: A2.9 (~ENABLE), J1.37 (GPIO26/SDIO_DAT2), U9.21 (NENBL)
/Pololu/IC2_step: A2.15 (STEP), J1.22 (GPIO25/SDIO_DAT1), U9.22 (STEP)
/Pololu/IC3_1A: A3.4 (1A), J18.3, JP69.2 (B)
/Pololu/IC3_1B: A3.3 (1B), J18.4, JP70.2 (B)
/Pololu/IC3_2A: A3.5 (2A), J18.2, JP72.2 (B)
/Pololu/IC3_2B: A3.6 (2B), J18.1, JP71.2 (B)
/Pololu/IC3_dir: A3.16 (DIR), J1.38 (GPIO20/SPI1_MOSI/PCM_DIN/PWM1), U12.20 (DIR)
/Pololu/IC3_enable: A3.9 (~ENABLE), J1.15 (GPIO22/SDIO_CLK), U12.21 (NENBL)
/Pololu/IC3_step: A3.15 (STEP), J1.40 (GPIO21/SPI1_SCLK/PCM_DOUT), U12.22 (STEP)
/Pololu/IC4_1A: A4.4 (1A), J19.3, JP65.2 (B)
/Pololu/IC4_1B: A4.3 (1B), J19.4, JP66.2 (B)
/Pololu/IC4_2A: A4.5 (2A), J19.2, JP68.2 (B)
/Pololu/IC4_2B: A4.6 (2B), J19.1, JP67.2 (B)
/Pololu/IC4_dir: A4.16 (DIR), U1.17 (GPA0), U11.20 (DIR)
/Pololu/IC4_enable: A4.9 (~ENABLE), U1.19 (GPA2), U11.21 (NENBL)
/Pololu/IC4_step: A4.15 (STEP), U1.18 (GPA1), U11.22 (STEP)
/Pololu/IC5_1A: A5.4 (1A), J20.3, JP61.2 (B)
/Pololu/IC5_1B: A5.3 (1B), J20.4, JP62.2 (B)
/Pololu/IC5_2A: A5.5 (2A), J20.2, JP64.2 (B)
/Pololu/IC5_2B: A5.6 (2B), J20.1, JP63.2 (B)
/Pololu/IC5_dir: A5.16 (DIR), U1.22 (GPA5), U10.20 (DIR)
/Pololu/IC5_enable: A5.9 (~ENABLE), U1.20 (GPA3), U10.21 (NENBL)
/Pololu/IC5_step: A5.15 (STEP), U1.21 (GPA4), U10.22 (STEP)
/Pololu/MS1_DRV8825_2: A2.10 (MS1), JP15.2 (B)
/Pololu/MS1_DRV8825_3: A3.10 (MS1), JP12.2 (B)
/Pololu/MS1_DRV8825_4: A4.10 (MS1), JP18.2 (B)
/Pololu/MS1_DRV8825_5: A5.10 (MS1), JP21.2 (B)
/Pololu/MS2_DRV8825_2: A2.11 (MS2), JP16.2 (B)
/Pololu/MS2_DRV8825_3: A3.11 (MS2), JP13.2 (B)
/Pololu/MS2_DRV8825_4: A4.11 (MS2), JP19.2 (B)
/Pololu/MS2_DRV8825_5: A5.11 (MS2), JP22.2 (B)
/Pololu/MS3_DRV8825_2: A2.12 (MS3), JP17.2 (B)
/Pololu/MS3_DRV8825_3: A3.12 (MS3), JP14.2 (B)
/Pololu/MS3_DRV8825_4: A4.12 (MS3), JP20.2 (B)
/Pololu/MS3_DRV8825_5: A5.12 (MS3), JP23.2 (B)
/Pololu/reset: A1.13 (~RESET), A2.13 (~RESET), A3.13 (~RESET), A4.13 (~RESET), A5.13 (~RESET), J1.16 (GPIO23/SDIO_CMD), U4.16 (nRESET), U9.16 (nRESET), U10.16 (nRESET), U11.16 (nRESET), U12.16 (nRESET)
/Pololu/sleep: A1.14 (~SLEEP), A2.14 (~SLEEP), A3.14 (~SLEEP), A4.14 (~SLEEP), A5.14 (~SLEEP), J1.35 (GPIO19/SPI1_MISO/PCM_FS), R6.1, R37.1, R41.1, R55.1, R59.1, U4.17 (nSLEEP), U9.17 (nSLEEP), U10.17 (nSLEEP), U11.17 (nSLEEP), U12.17 (nSLEEP)
/buttons/sw_limit_4: R19.2, SW9.1
/buttons/sw_limit_5: R20.2, SW10.1
/flt_1: R5.2, R6.2, U1.23 (GPA6)
/flt_2: R36.2, R37.2, U1.24 (GPA7)
/flt_3: R58.2, R59.2, U1.25 (GPB0)
/limit_1: J1.26 (~CE1_SPI0/GPIO07), R16.2, SW6.1
/limit_2: J1.28 (ID_SC_I2C0/GPIO01), R17.2, SW7.1
/limit_3: J1.7 (GPCLK0/GPIO04), R18.2, SW8.1
/switch_a: J1.11 (GPIO17/SPI1_~CE1), R14.2, SW5.1
/switch_b: J1.36 (GPIO16/SPI1_~CE2), R15.2, SW4.1
/switch_c: J1.31 (GPCLK2/GPIO06), R10.2, SW3.1
/switch_d: J1.29 (GPCLK1/GPIO05), R11.2, SW2.1
GND: A1.1 (GND), A1.7 (GND), A2.1 (GND), A2.7 (GND), A3.1 (GND), A3.7 (GND), A4.1 (GND), A4.7 (GND), A5.1 (GND), A5.7 (GND), C1.2, C2.2, C3.2, C4.2, C5.2, C6.2, C7.2, C8.2, C9.2, C10.2, C11.2, C12.2, C13.2, C14.1, C15.1, C17.2, C32.2, C33.2, C34.2, C35.2, C36.2, C37.2, C38.1, C39.2, C40.2, C41.2, C42.2, C43.2, C48.2, C49.2, C50.2, C53.2, C56.2, C63.2, J1.6 (GND), J1.9 (GND), J1.14 (GND), J1.20 (GND), J1.25 (GND), J1.30 (GND), J1.34 (GND), J1.39 (GND), J3.2 (Ext), J21.6, J23.1, J24.6 (VSS), R1.2, R2.1, R3.2, R4.2, R13.2, R34.2, R35.1, R38.2, R39.1, R43.2, R50.2, R51.2, R52.2, R53.1, R56.2, R57.1, RV1.3, RV5.3, RV6.3, RV7.3, RV8.3, SW2.2, SW3.2, SW4.2, SW5.2, SW6.2, SW7.2, SW8.2, SW9.2, SW10.2, U1.6 (V_{SS}), U1.11 (A0), U1.12 (A1), U1.13 (A2), U2.1 (GND), U3.1 (GND), U4.14 (GND), U4.28 (GND), U4.29 (EP), U9.14 (GND), U9.28 (GND), U9.29 (EP), U10.14 (GND), U10.28 (GND), U10.29 (EP), U11.14 (GND), U11.28 (GND), U11.29 (EP), U12.14 (GND), U12.28 (GND), U12.29 (EP)
unnamed: C11.1, D2.2 (A), U3.2 (VO)
unnamed: D3.2 (A), J3.1 (In)
unnamed: D6.1 (K), R3.1
unnamed: D7.1 (K), R50.1
unnamed: D8.1 (K), R51.1
unnamed: D9.1 (K), R4.1
unnamed: D10.1 (K), R52.1
unnamed: J24.8 (DAT1), R49.2
unnamed: J24.1 (DAT2), R48.1
unnamed: JP25.1 (A), U4.7 (AOUT2)
unnamed: JP26.1 (A), U4.5 (AOUT1)
unnamed: JP27.1 (A), U4.8 (BOUT2)
unnamed: JP28.1 (A), U4.10 (BOUT1)
unnamed: JP57.1 (A), U9.5 (AOUT1)
unnamed: JP58.1 (A), U9.7 (AOUT2)
unnamed: JP59.1 (A), U9.8 (BOUT2)
unnamed: JP60.1 (A), U9.10 (BOUT1)
unnamed: JP61.1 (A), U10.5 (AOUT1)
unnamed: JP62.1 (A), U10.7 (AOUT2)
unnamed: JP63.1 (A), U10.8 (BOUT2)
unnamed: JP64.1 (A), U10.10 (BOUT1)
unnamed: JP65.1 (A), U11.5 (AOUT1)
unnamed: JP66.1 (A), U11.7 (AOUT2)
unnamed: JP67.1 (A), U11.8 (BOUT2)
unnamed: JP68.1 (A), U11.10 (BOUT1)
unnamed: JP69.1 (A), U12.5 (AOUT1)
unnamed: JP70.1 (A), U12.7 (AOUT2)
unnamed: JP71.1 (A), U12.8 (BOUT2)
unnamed: JP72.1 (A), U12.10 (BOUT1)
unnamed: R12.2, SW1.1
unnamed: R7.2, U1.14 (~RESET)
unnamed: C14.2, C38.2, L1.2, U2.3 (VI)
unnamed: RV1.2, U4.12 (AVREF), U4.13 (BVREF)
unnamed: C16.1, U4.1 (CP1)
unnamed: C16.2, U4.2 (CP2)
unnamed: R1.1, U4.6 (ISENA)
unnamed: R2.2, U4.9 (ISENB)
unnamed: C17.1, U4.15 (V3P3OUT)
unnamed: C18.2, U4.3 (VCP)
unnamed: R5.1, U4.18 (nFAULT)
unnamed: RV5.2, U9.12 (AVREF), U9.13 (BVREF)
unnamed: C30.1, U9.1 (CP1)
unnamed: C30.2, U9.2 (CP2)
unnamed: R34.1, U9.6 (ISENA)
unnamed: R35.2, U9.9 (ISENB)
unnamed: C37.1, U9.15 (V3P3OUT)
unnamed: C28.2, U9.3 (VCP)
unnamed: R36.1, U9.18 (nFAULT)
unnamed: RV6.2, U10.12 (AVREF), U10.13 (BVREF)
unnamed: C46.1, U10.1 (CP1)
unnamed: C46.2, U10.2 (CP2)
unnamed: R38.1, U10.6 (ISENA)
unnamed: R39.2, U10.9 (ISENB)
unnamed: C53.1, U10.15 (V3P3OUT)
unnamed: C44.2, U10.3 (VCP)
unnamed: R40.1, U10.18 (nFAULT)
unnamed: RV7.2, U11.12 (AVREF), U11.13 (BVREF)
unnamed: C55.1, U11.1 (CP1)
unnamed: C55.2, U11.2 (CP2)
unnamed: R43.1, U11.6 (ISENA)
unnamed: R53.2, U11.9 (ISENB)
unnamed: C56.1, U11.15 (V3P3OUT)
unnamed: C54.2, U11.3 (VCP)
unnamed: R54.1, U11.18 (nFAULT)
unnamed: RV8.2, U12.12 (AVREF), U12.13 (BVREF)
unnamed: C62.1, U12.1 (CP1)
unnamed: C62.2, U12.2 (CP2)
unnamed: R56.1, U12.6 (ISENA)
unnamed: R57.2, U12.9 (ISENB)
unnamed: C63.1, U12.15 (V3P3OUT)
unnamed: C61.2, U12.3 (VCP)
unnamed: R58.1, U12.18 (nFAULT)
SW_PWR: R13.1, SW1.2
VCC: A1.8 (VMOT), A2.8 (VMOT), A3.8 (VMOT), A4.8 (VMOT), A5.8 (VMOT), C18.1, C28.1, C32.1, C33.1, C34.1, C35.1, C36.1, C39.1, C40.1, C41.1, C44.1, C48.1, C49.1, C50.1, C54.1, C61.1, D3.1 (K), R12.1, U3.3 (VI), U4.4 (VMA), U4.11 (VMB), U9.4 (VMA), U9.11 (VMB), U10.4 (VMA), U10.11 (VMB), U11.4 (VMA), U11.11 (VMB), U12.4 (VMA), U12.11 (VMB)

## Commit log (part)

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2026-06-13 Project CNC Raspberry pi 2w PCB SCH Kicad
2026-06-13 add files
2026-06-29 moove docs md to docs
